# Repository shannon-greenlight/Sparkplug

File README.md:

# Sparkplug
Signal Monitor Device

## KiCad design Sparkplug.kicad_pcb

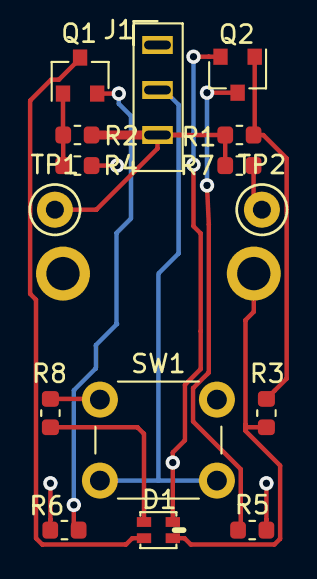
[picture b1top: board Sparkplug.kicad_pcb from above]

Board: 2 copper layers, 16 parts (1 on the bottom side), 12 nets.

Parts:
BT1: Batt Holder; BatteryHolder_Keystone_3031_1x10mm
D1: LED_RGBA; LED_RGBA1.6mm
J1: AudioJack3; Plug_TRS
Q1: MMBT3904; SOT-23
Q2: MMBT3906; SOT-23
R1, R2, R7: 100K; R_0603_1608Metric
R3: 330K; R_0603_1608Metric
R4: 300K; R_0603_1608Metric
R5, R6: 100; R_0603_1608Metric
R8: 270; R_0603_1608Metric
SW1: SW_Push_Dual; SW_PUSH_6mm
TP1, TP2: TestPoint; TestPoint_Keystone_5000-5004_Miniature

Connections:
GND: J1.S, R4.1, R5.2, R6.2, R7.1, TP2.1
unnamed: BT1.1, D1.4, R3.2
unnamed: BT1.2, J1.R, SW1.2
unnamed: D1.1, Q1.3
unnamed: D1.2, R8.1
unnamed: D1.3, Q2.2
unnamed: J1.T, R1.2, R2.2, R7.2, TP1.1
unnamed: Q1.1, R2.1, R4.2
unnamed: Q1.2, R6.1
unnamed: Q2.1, R1.1, R3.1
unnamed: Q2.3, R5.1
unnamed: R8.2, SW1.1

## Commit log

2020-08-18 Added files
2020-08-18 Removed unneeded files. Added files required by builder.
2020-08-18 Adds orig files
2020-08-19 Adds spice file
